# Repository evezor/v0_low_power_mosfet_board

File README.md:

# Low Power Mosfet Board
*please note this board has been deprecated.

An edge board containing 3 low power mosfets capable of powering small loads like relays, small fans and LEDs. Also 3 buttons.  Each output may be pulse width modulated.  Power can come from the bus or external sources, selectable by jumper.

source files can be found here: https://github.com/evezor/v0_low_power_mosfet_board

This board uses the Evezor Stamp STMF405 MCU

source: https://github.com/evezor/Evezor-Stamp-STMF405

Evezor® and all associated marks, logos, and designs are registered trademarks and protected by copyright. Unauthorized use or reproduction of these trademarks and copyrighted materials is strictly prohibited.

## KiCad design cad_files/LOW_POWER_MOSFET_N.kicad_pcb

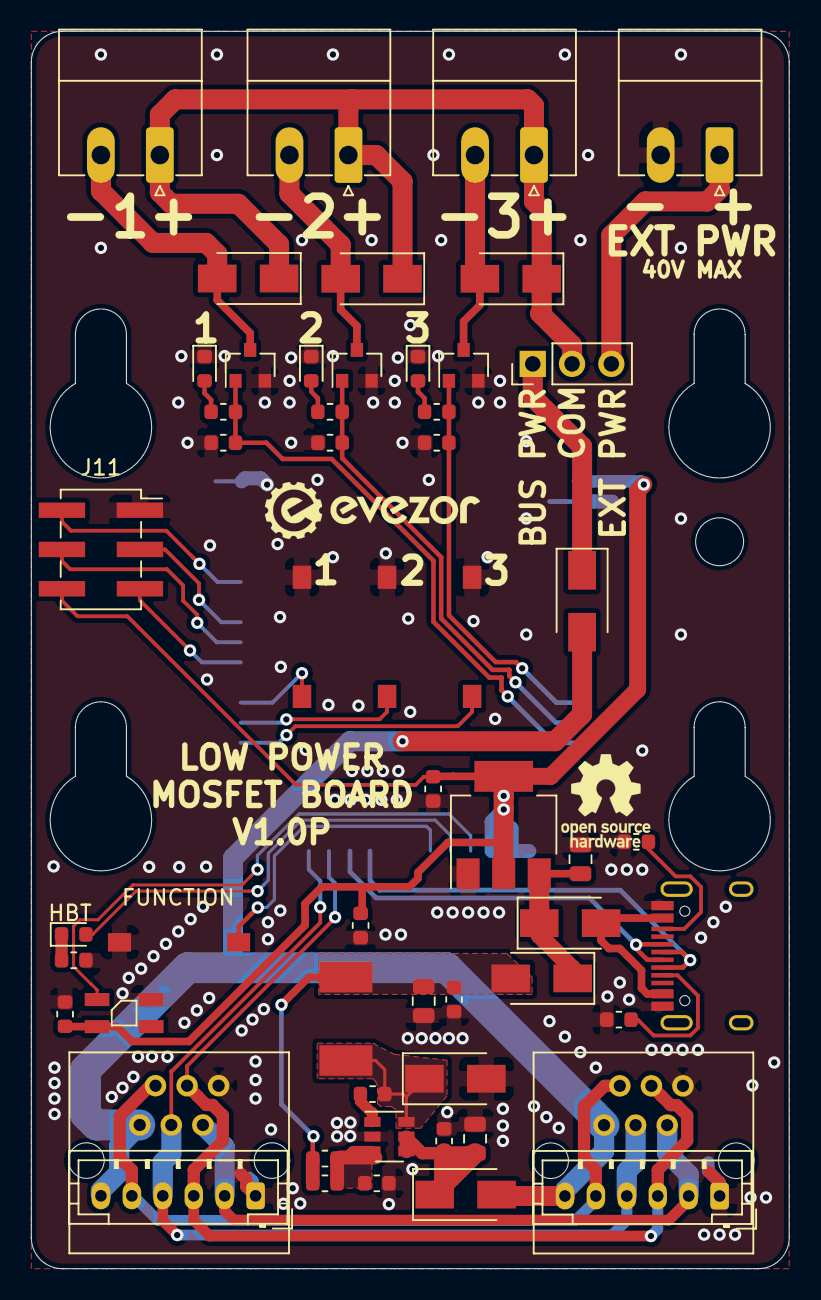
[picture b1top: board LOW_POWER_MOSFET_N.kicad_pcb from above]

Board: 2 copper layers, 49.0 x 80.0 mm, 57 parts (1 on the bottom side), 41 nets.

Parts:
C1, C2, C3, C5, C8, C9: .1uF; C_0603_1608Metric
C4: 4.7uF; C_0805_2012Metric
C6: 22uF; C_0805_2012Metric
C7: 10uF; C_0805_2012Metric
C10: C_Small; C_0603_1608Metric
D1, D2, D3, D11: LED; LED_0603_1608Metric
D4, D8, D9, D10, D13: SX35_SCHOTTKY; D_SMA
D5, D6, D7: D; D_SMA
D12: SK6812MINI; LED_SK6812MINI_PLCC4_3.5x3.5mm_P1.75mm
H1: MountingHole; OLED_STANDOFF
J1: PWR_JUMPER; PinHeader_1x03_P2.54mm_Vertical
J2, J3, J4, J5: Conn_01x02; PhoenixContact_MC_1,5_2-G-3.81_1x02_P3.81mm_Horizontal
J6: USB_C_Receptacle_USB2.0; USB_C_Receptacle_HRO_TYPE-C-31-M-12
J7, J8: PH; JST_PH_B6B-PH-K_1x06_P2.00mm_Vertical
J9, J10: RJ11; RJ11_C189747_Horizontal
J11: Conn_02x03_Odd_Even; OLED_HEADER
L1: 22uH; INDUCTOR_7.5X6.6_GCDA0630-220MC
Q1, Q2, Q3: T2N7002BK,LM‎; SOT-23
R1, R13: 15k; R_0603_1608Metric
R2, R4, R6: 1k; R_0603_1608Metric
R3, R5, R7: 10k; R_0603_1608Metric
R8: 82k; R_0603_1608Metric
R9, R10: 5.1k; R_0603_1608Metric
SW1, SW2, SW3, SW4: SW_Push; SWITCH_2x3_SMD_TACTILE_GREEN
U1: SY8401ABC; SOT-23-6
U2: AMS1117-3.3; SOT-223-3_TabPin2
U3: EDGE_STM32F405_CPU_V1; EDGE_STAMP

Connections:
+3V3: C8.1, C9.1, C10.2, D12.4, J11.6, U2.2, U3.1, U3.18
+48V: D8.2, D13.2, J7.6, J8.6, J9.6, J10.6
/BOOT: J11.3, U3.36
/BUTTON_1: SW2.1, U3.32
/BUTTON_2: SW3.1, U3.31
/BUTTON_3: SW4.1, U3.30
/CAN_H: J7.3, J8.3, J9.3, J10.3, U3.26
/CAN_L: J7.4, J8.4, J9.4, J10.4, U3.27
/CC1: J6.A5, R10.1
/CC2: J6.B5, R9.1
/D+: J6.A6, J6.B6, U3.25
/D-: J6.A7, J6.B7, U3.24
/FD_H: J7.2, J8.2, J9.2, J10.2
/FD_L: J7.5, J8.5, J9.5, J10.5
/FET_1: Q1.1, R2.1, R3.2, U3.14
/FET_2: Q2.1, R4.1, R5.2, U3.13
/FET_3: Q3.1, R6.1, R7.2, U3.12
/FUNCTION_BUTTON: SW1.1, U3.21
/HBT_LED: D11.2, U3.20
/NEO_STATUS: D12.3, U3.19
/OLED_SCL: J11.5, U3.34
/OLED_SDA: J11.4, U3.35
/RESET: J11.2, U3.38
/USB_VCC: D9.2, J6.A4, J6.A9, J6.B4, J6.B9
/VREG_OUT: C2.1, C5.1, C6.1, D10.2, L1.2, R8.1
/Vout: D5.1, D6.1, D7.1, J1.2, J3.1, J4.1, J5.1
GND: C3.2, C4.2, C5.2, C6.2, C7.2, C8.2, C9.2, C10.1, D1.1, D2.1, D3.1, D4.2, D12.2, J2.2, J6.A1, J6.A12, J6.B1, J6.B12, J7.1, J8.1, J9.1, J10.1, J11.1, Q1.2, Q2.2, Q3.2, R1.1, R3.1, R5.1, R7.1, R9.2, R10.2, R13.1, SW1.2, SW2.2, SW3.2, SW4.2, U1.2, U2.1, U3.2, U3.17, U3.43
unnamed: C1.1, D4.1, L1.1, U1.6
unnamed: C1.2, U1.1
unnamed: C2.2, R1.2, R8.2, U1.3
unnamed: C3.1, C4.1, D8.1, U1.4, U1.5
unnamed: C7.1, D9.1, D10.1, U2.3
unnamed: D1.2, R2.2
unnamed: D2.2, R4.2
unnamed: D3.2, R6.2
unnamed: D5.2, J3.2, Q1.3
unnamed: D6.2, J4.2, Q2.3
unnamed: D7.2, J5.2, Q3.3
unnamed: D11.1, R13.2
unnamed: D13.1, J1.1
VBUS: J1.3, J2.1

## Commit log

2020-11-26 Add testcode and remove unneded silkscreen
2023-09-11 Create LICENSE
2023-09-11 add pics
2023-09-11 add schematics
